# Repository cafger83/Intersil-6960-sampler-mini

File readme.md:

This board set is a small and light version of the original Intersil 6960 Sampler board.
Schematic based on the manual of the original board.
The CPU (IM6101) is a one-chip implementation of the legendary DEC PDP-8 computer's CPU

Boards:
IM6100 SAMPLER mini - main board with CPU, serial port, 1kword ROM monitor and 256 kword RAM

IM6100 HID - human interface device with status leds, address display, 12x input switches

IM6100 RAM+IO - 2kword RAM extension, 2x12bit GPIO

Original board:
https://computermuseum.informatik.uni-stuttgart.de/dev_en/im6100sp/

Original manual:
http://dunfield.classiccmp.org/other/i6100cfs.pdf

*** UNDER DEVELOPMENT! Not tested, not validated yet. ***

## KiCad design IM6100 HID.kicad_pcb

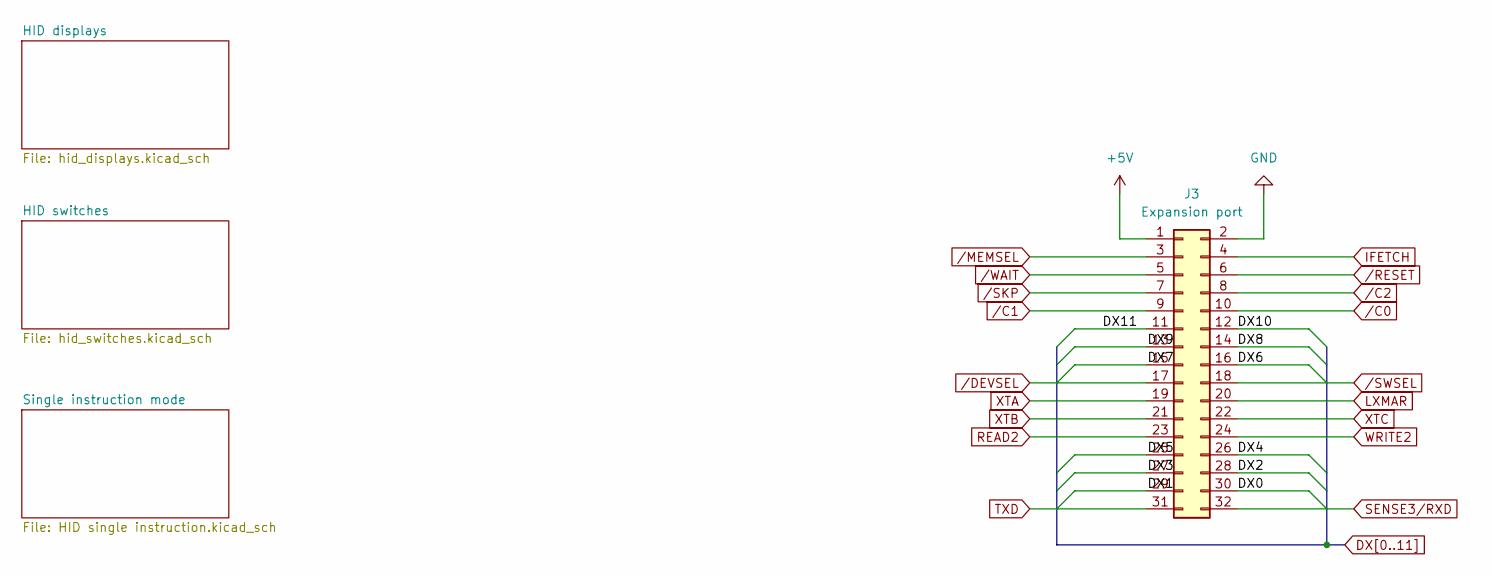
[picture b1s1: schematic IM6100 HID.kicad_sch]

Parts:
J3: Expansion port; PinHeader_2x16_P2.54mm_Vertical

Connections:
+5V: J3.1; also elsewhere on the board
DX0: J3.30; also elsewhere on the board
DX1: J3.29; also elsewhere on the board
DX2: J3.28; also elsewhere on the board
DX3: J3.27; also elsewhere on the board
DX4: J3.26; also elsewhere on the board
DX5: J3.25; also elsewhere on the board
DX6: J3.16; also elsewhere on the board
DX7: J3.15; also elsewhere on the board
DX8: J3.14; also elsewhere on the board
DX9: J3.13; also elsewhere on the board
DX10: J3.12; also elsewhere on the board
DX11: J3.11; also elsewhere on the board
GND: J3.2; also elsewhere on the board
IFETCH: J3.4; also elsewhere on the board
LXMAR: J3.20; also elsewhere on the board
READ2: J3.23
TXD: J3.31; also elsewhere on the board
WRITE2: J3.24
XTA: J3.19
XTB: J3.21; also elsewhere on the board
XTC: J3.22; also elsewhere on the board
/C0: J3.10
/C1: J3.9
/C2: J3.8
/RESET: J3.6; also elsewhere on the board
/SKP: J3.7
/WAIT: J3.5; also elsewhere on the board

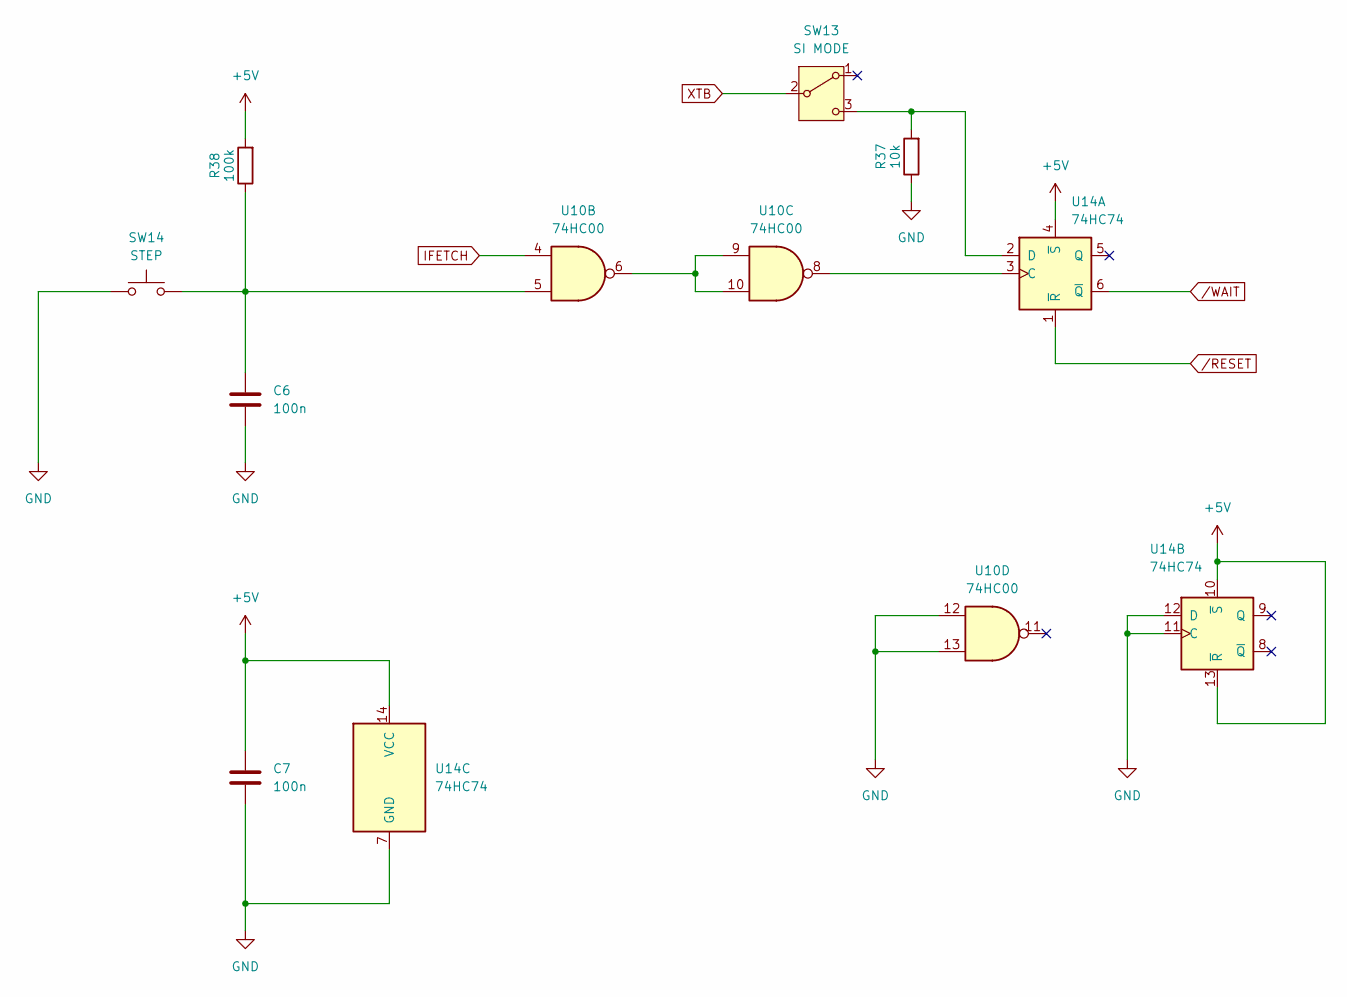
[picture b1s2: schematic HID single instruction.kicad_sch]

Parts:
C6, C7: 100n; C_0805_2012Metric_Pad1.18x1.45mm_HandSolder
R37: 10k; R_0805_2012Metric
R38: 100k; R_0805_2012Metric
SW13: SI MODE; PinHeader_1x03_P2.54mm_Vertical
SW14: STEP; SW_PUSH_6mm_H4.3mm
U10: 74HC00; SO-14_3.9x8.65mm_P1.27mm
U14: 74HC74; SO-14_3.9x8.65mm_P1.27mm

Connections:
+5V: C7.1, R38.2, U14.4 (~S), U14.10 (~S), U14.13 (~R), U14.14 (VCC); also elsewhere on the board
GND: C6.2, C7.2, R37.1, SW14.1, U10.12, U10.13, U14.7 (GND), U14.11 (C), U14.12 (D); also elsewhere on the board
IFETCH: U10.4; also elsewhere on the board
unnamed: C6.1, R38.1, SW14.2, U10.5
unnamed: R37.2, SW13.3 (C), U14.2 (D)
unnamed: U10.6, U10.9, U10.10
unnamed: U10.8, U14.3 (C)
XTB: SW13.2 (B); also elsewhere on the board
/RESET: U14.1 (~R); also elsewhere on the board
/WAIT: U14.6 (~Q); also elsewhere on the board

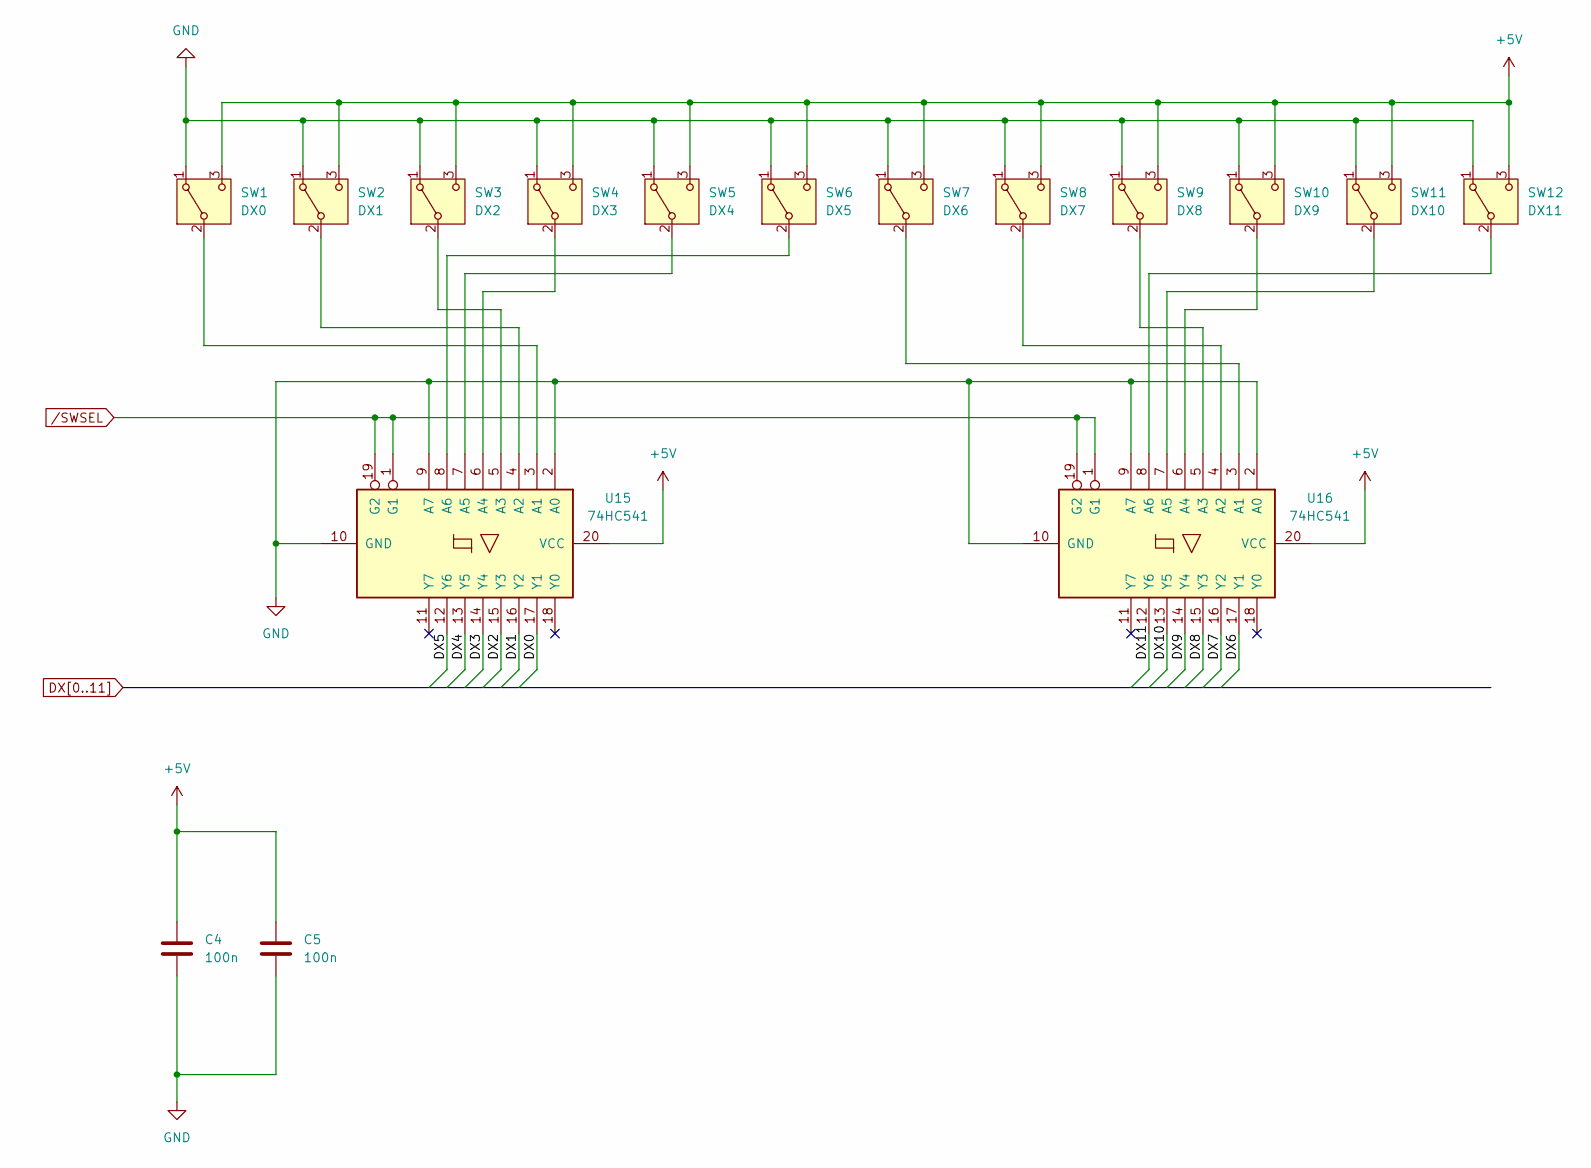
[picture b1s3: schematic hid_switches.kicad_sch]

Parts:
C4, C5: 100n; C_0805_2012Metric_Pad1.18x1.45mm_HandSolder
SW1: DX0; PinHeader_1x03_P2.54mm_Vertical
SW2: DX1; PinHeader_1x03_P2.54mm_Vertical
SW3: DX2; PinHeader_1x03_P2.54mm_Vertical
SW4: DX3; PinHeader_1x03_P2.54mm_Vertical
SW5: DX4; PinHeader_1x03_P2.54mm_Vertical
SW6: DX5; PinHeader_1x03_P2.54mm_Vertical
SW7: DX6; PinHeader_1x03_P2.54mm_Vertical
SW8: DX7; PinHeader_1x03_P2.54mm_Vertical
SW9: DX8; PinHeader_1x03_P2.54mm_Vertical
SW10: DX9; PinHeader_1x03_P2.54mm_Vertical
SW11: DX10; PinHeader_1x03_P2.54mm_Vertical
SW12: DX11; PinHeader_1x03_P2.54mm_Vertical
U15, U16: 74HC541; SO-20_12.8x7.5mm_P1.27mm

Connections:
+5V: C4.1, C5.1, SW1.3 (C), SW2.3 (C), SW3.3 (C), SW4.3 (C), SW5.3 (C), SW6.3 (C), SW7.3 (C), SW8.3 (C), SW9.3 (C), SW10.3 (C), SW11.3 (C), SW12.3 (C), U15.20 (VCC), U16.20 (VCC); also elsewhere on the board
DX0: U15.17 (Y1); also elsewhere on the board
DX1: U15.16 (Y2); also elsewhere on the board
DX2: U15.15 (Y3); also elsewhere on the board
DX3: U15.14 (Y4); also elsewhere on the board
DX4: U15.13 (Y5); also elsewhere on the board
DX5: U15.12 (Y6); also elsewhere on the board
DX6: U16.17 (Y1); also elsewhere on the board
DX7: U16.16 (Y2); also elsewhere on the board
DX8: U16.15 (Y3); also elsewhere on the board
DX9: U16.14 (Y4); also elsewhere on the board
DX10: U16.13 (Y5); also elsewhere on the board
DX11: U16.12 (Y6); also elsewhere on the board
GND: C4.2, C5.2, SW1.1 (A), SW2.1 (A), SW3.1 (A), SW4.1 (A), SW5.1 (A), SW6.1 (A), SW7.1 (A), SW8.1 (A), SW9.1 (A), SW10.1 (A), SW11.1 (A), SW12.1 (A), U15.2 (A0), U15.9 (A7), U15.10 (GND), U16.2 (A0), U16.9 (A7), U16.10 (GND); also elsewhere on the board
unnamed: SW1.2 (B), U15.3 (A1)
unnamed: SW2.2 (B), U15.4 (A2)
unnamed: SW3.2 (B), U15.5 (A3)
unnamed: SW4.2 (B), U15.6 (A4)
unnamed: SW5.2 (B), U15.7 (A5)
unnamed: SW6.2 (B), U15.8 (A6)
unnamed: SW7.2 (B), U16.3 (A1)
unnamed: SW8.2 (B), U16.4 (A2)
unnamed: SW9.2 (B), U16.5 (A3)
unnamed: SW10.2 (B), U16.6 (A4)
unnamed: SW11.2 (B), U16.7 (A5)
unnamed: SW12.2 (B), U16.8 (A6)

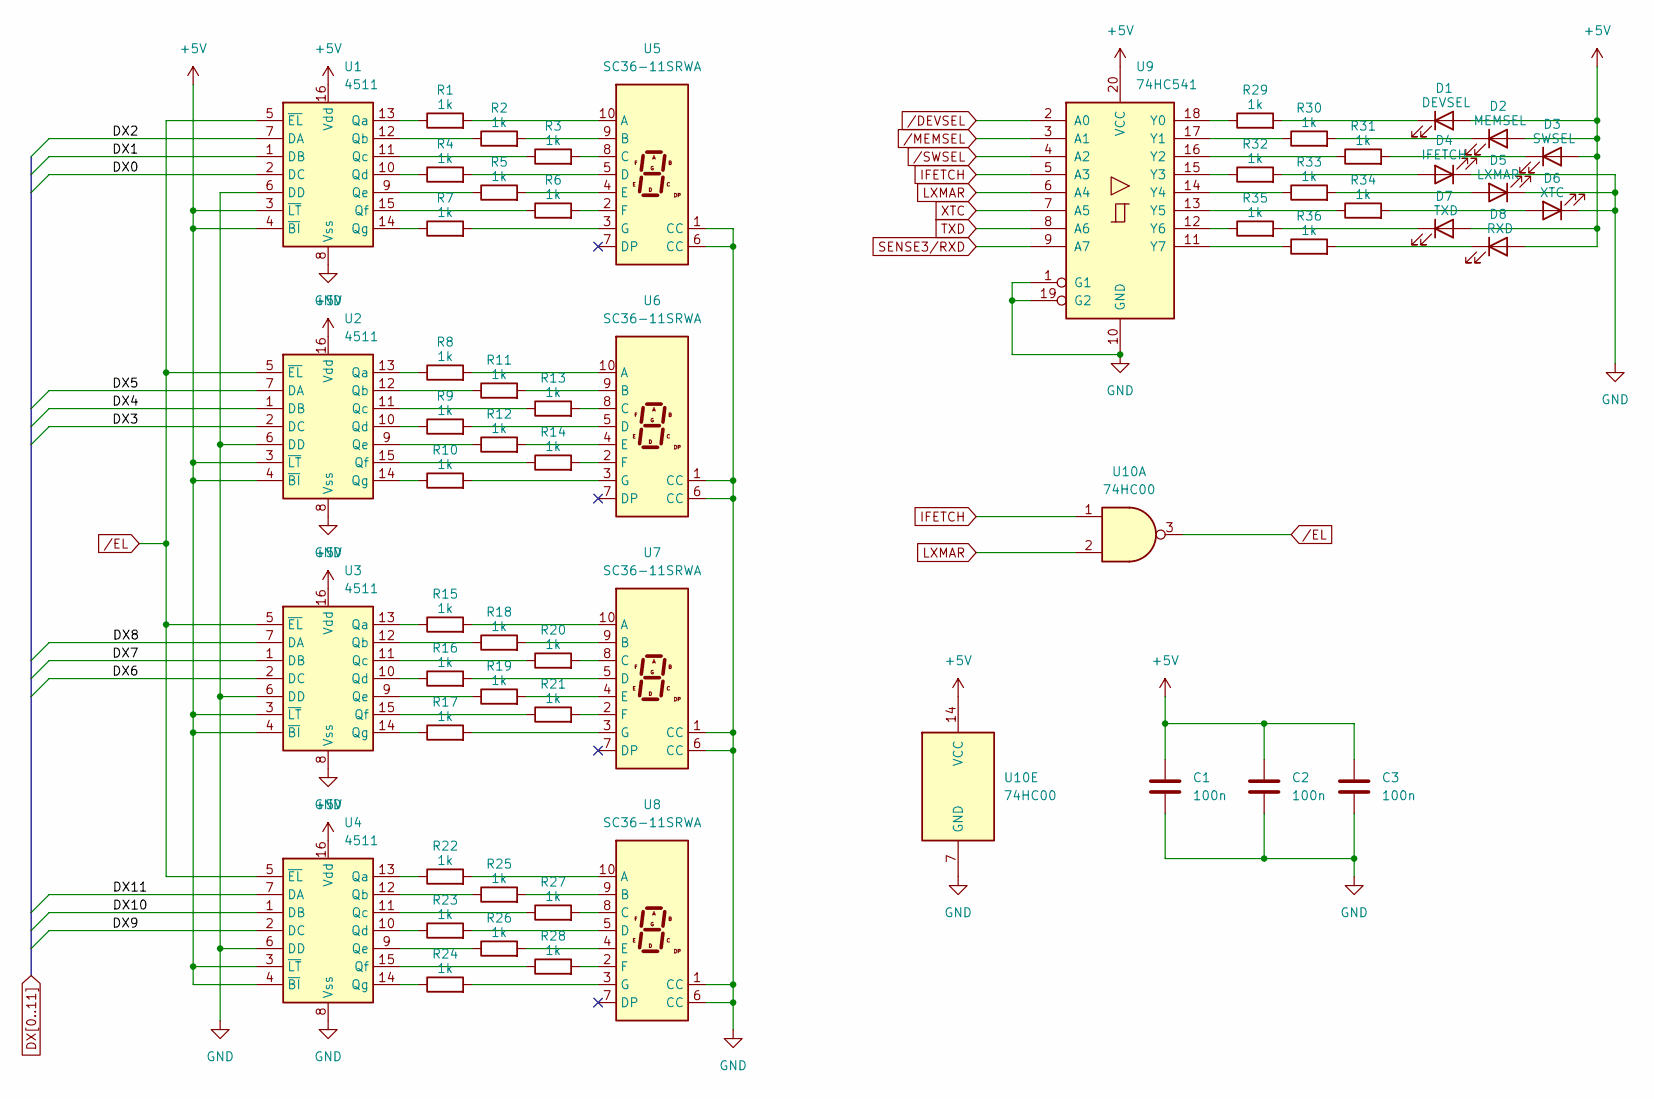
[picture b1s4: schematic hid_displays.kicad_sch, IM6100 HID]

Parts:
C1, C2, C3: 100n; C_0805_2012Metric_Pad1.18x1.45mm_HandSolder
D1: DEVSEL; LED_1206_3216Metric
D2: MEMSEL; LED_1206_3216Metric
D3: SWSEL; LED_1206_3216Metric
D4: IFETCH; LED_1206_3216Metric
D5: LXMAR; LED_1206_3216Metric
D6: XTC; LED_1206_3216Metric
D7: TXD; LED_1206_3216Metric
D8: RXD; LED_1206_3216Metric
R1, R2, R3, R4, R5, R6, R7, R8, R9, R10, R11, R12, R13, R14, R15, R16, R17, R18, R19, R20, R21, R22, R23, R24, R25, R26, R27, R28, R29, R30, R31, R32, R33, R34, R35, R36: 1k; R_0805_2012Metric
U1, U2, U3, U4: 4511; SO-16_3.9x9.9mm_P1.27mm
U5, U6, U7, U8: SC36-11SRWA; HDSP-A151
U9: 74HC541; SO-20_12.8x7.5mm_P1.27mm
U10: 74HC00; SO-14_3.9x8.65mm_P1.27mm

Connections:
+5V: C1.1, C2.1, C3.1, D1.2 (A), D2.2 (A), D3.2 (A), D7.2 (A), D8.2 (A), U1.3 (~LT), U1.4 (~BI), U1.16 (Vdd), U2.3 (~LT), U2.4 (~BI), U2.16 (Vdd), U3.3 (~LT), U3.4 (~BI), U3.16 (Vdd), U4.3 (~LT), U4.4 (~BI), U4.16 (Vdd), U9.20 (VCC), U10.14 (VCC); also elsewhere on the board
DX0: U1.2 (DC); also elsewhere on the board
DX1: U1.1 (DB); also elsewhere on the board
DX2: U1.7 (DA); also elsewhere on the board
DX3: U2.2 (DC); also elsewhere on the board
DX4: U2.1 (DB); also elsewhere on the board
DX5: U2.7 (DA); also elsewhere on the board
DX6: U3.2 (DC); also elsewhere on the board
DX7: U3.1 (DB); also elsewhere on the board
DX8: U3.7 (DA); also elsewhere on the board
DX9: U4.2 (DC); also elsewhere on the board
DX10: U4.1 (DB); also elsewhere on the board
DX11: U4.7 (DA); also elsewhere on the board
GND: C1.2, C2.2, C3.2, D4.1 (K), D5.1 (K), D6.1 (K), U1.6 (DD), U1.8 (Vss), U2.6 (DD), U2.8 (Vss), U3.6 (DD), U3.8 (Vss), U4.6 (DD), U4.8 (Vss), U5.1 (CC), U5.6 (CC), U6.1 (CC), U6.6 (CC), U7.1 (CC), U7.6 (CC), U8.1 (CC), U8.6 (CC), U9.1 (G1), U9.10 (GND), U9.19 (G2), U10.7 (GND); also elsewhere on the board
IFETCH: U9.5 (A3), U10.1; also elsewhere on the board
LXMAR: U9.6 (A4), U10.2; also elsewhere on the board
unnamed: D1.1 (K), R29.2
unnamed: D2.1 (K), R30.2
unnamed: D3.1 (K), R31.2
unnamed: D4.2 (A), R32.2
unnamed: D5.2 (A), R33.2
unnamed: D6.2 (A), R34.2
unnamed: D7.1 (K), R35.2
unnamed: D8.1 (K), R36.2
unnamed: R1.1, U1.13 (Qa)
unnamed: R2.1, U1.12 (Qb)
unnamed: R3.1, U1.11 (Qc)
unnamed: R4.1, U1.10 (Qd)
unnamed: R5.1, U1.9 (Qe)
unnamed: R6.1, U1.15 (Qf)
unnamed: R7.1, U1.14 (Qg)
unnamed: R8.1, U2.13 (Qa)
unnamed: R11.1, U2.12 (Qb)
unnamed: R13.1, U2.11 (Qc)
unnamed: R9.1, U2.10 (Qd)
unnamed: R12.1, U2.9 (Qe)
unnamed: R14.1, U2.15 (Qf)
unnamed: R10.1, U2.14 (Qg)
unnamed: R15.1, U3.13 (Qa)
unnamed: R18.1, U3.12 (Qb)
unnamed: R20.1, U3.11 (Qc)
unnamed: R16.1, U3.10 (Qd)
unnamed: R19.1, U3.9 (Qe)
unnamed: R21.1, U3.15 (Qf)
unnamed: R17.1, U3.14 (Qg)
unnamed: R22.1, U4.13 (Qa)
unnamed: R25.1, U4.12 (Qb)
unnamed: R27.1, U4.11 (Qc)
unnamed: R23.1, U4.10 (Qd)
unnamed: R26.1, U4.9 (Qe)
unnamed: R28.1, U4.15 (Qf)
unnamed: R24.1, U4.14 (Qg)
unnamed: R1.2, U5.10 (A)
unnamed: R2.2, U5.9 (B)
unnamed: R3.2, U5.8 (C)
unnamed: R4.2, U5.5 (D)
unnamed: R5.2, U5.4 (E)
unnamed: R6.2, U5.2 (F)
unnamed: R7.2, U5.3 (G)
unnamed: R8.2, U6.10 (A)
unnamed: R11.2, U6.9 (B)
unnamed: R13.2, U6.8 (C)
unnamed: R9.2, U6.5 (D)
unnamed: R12.2, U6.4 (E)
unnamed: R14.2, U6.2 (F)
unnamed: R10.2, U6.3 (G)
unnamed: R15.2, U7.10 (A)
unnamed: R18.2, U7.9 (B)
unnamed: R20.2, U7.8 (C)
unnamed: R16.2, U7.5 (D)
unnamed: R19.2, U7.4 (E)
unnamed: R21.2, U7.2 (F)
unnamed: R17.2, U7.3 (G)
unnamed: R22.2, U8.10 (A)
unnamed: R25.2, U8.9 (B)
unnamed: R27.2, U8.8 (C)
unnamed: R23.2, U8.5 (D)
unnamed: R26.2, U8.4 (E)
unnamed: R28.2, U8.2 (F)
unnamed: R24.2, U8.3 (G)
unnamed: R29.1, U9.18 (Y0)
unnamed: R30.1, U9.17 (Y1)
unnamed: R31.1, U9.16 (Y2)
unnamed: R32.1, U9.15 (Y3)
unnamed: R33.1, U9.14 (Y4)
unnamed: R34.1, U9.13 (Y5)
unnamed: R35.1, U9.12 (Y6)
unnamed: R36.1, U9.11 (Y7)
TXD: U9.8 (A6); also elsewhere on the board
XTC: U9.7 (A5); also elsewhere on the board
/EL: U1.5 (~EL), U2.5 (~EL), U3.5 (~EL), U4.5 (~EL), U10.3

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
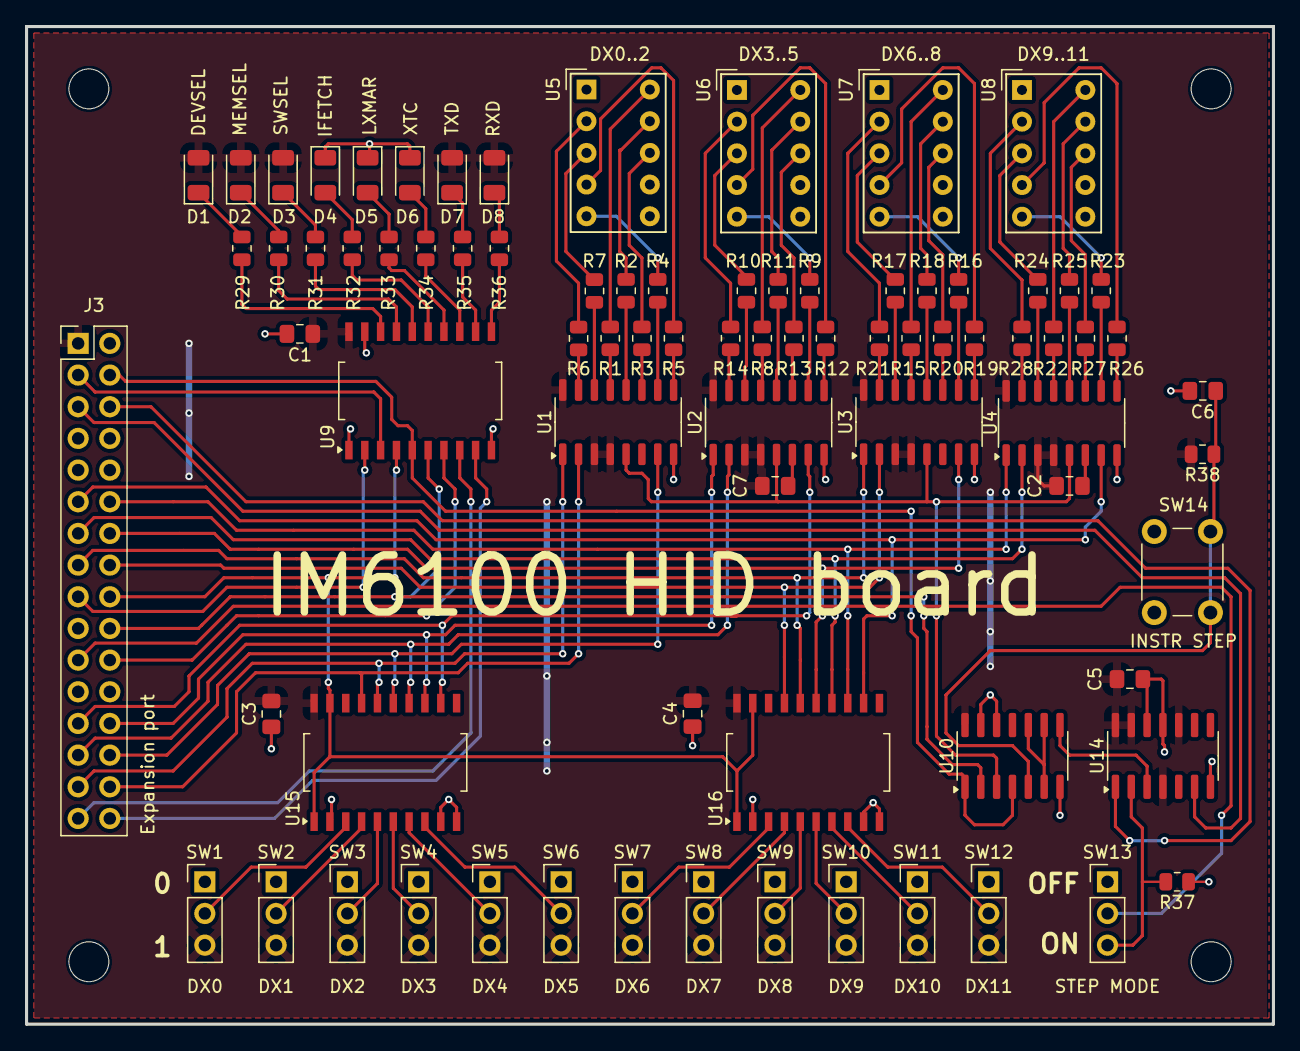
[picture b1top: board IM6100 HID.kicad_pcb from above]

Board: 2 copper layers, 100.0 x 80.0 mm, 85 parts (0 on the bottom side), 114 nets.

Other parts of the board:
HOLE1, HOLE2, HOLE3, HOLE4: MountingHole_3.2mm_M3

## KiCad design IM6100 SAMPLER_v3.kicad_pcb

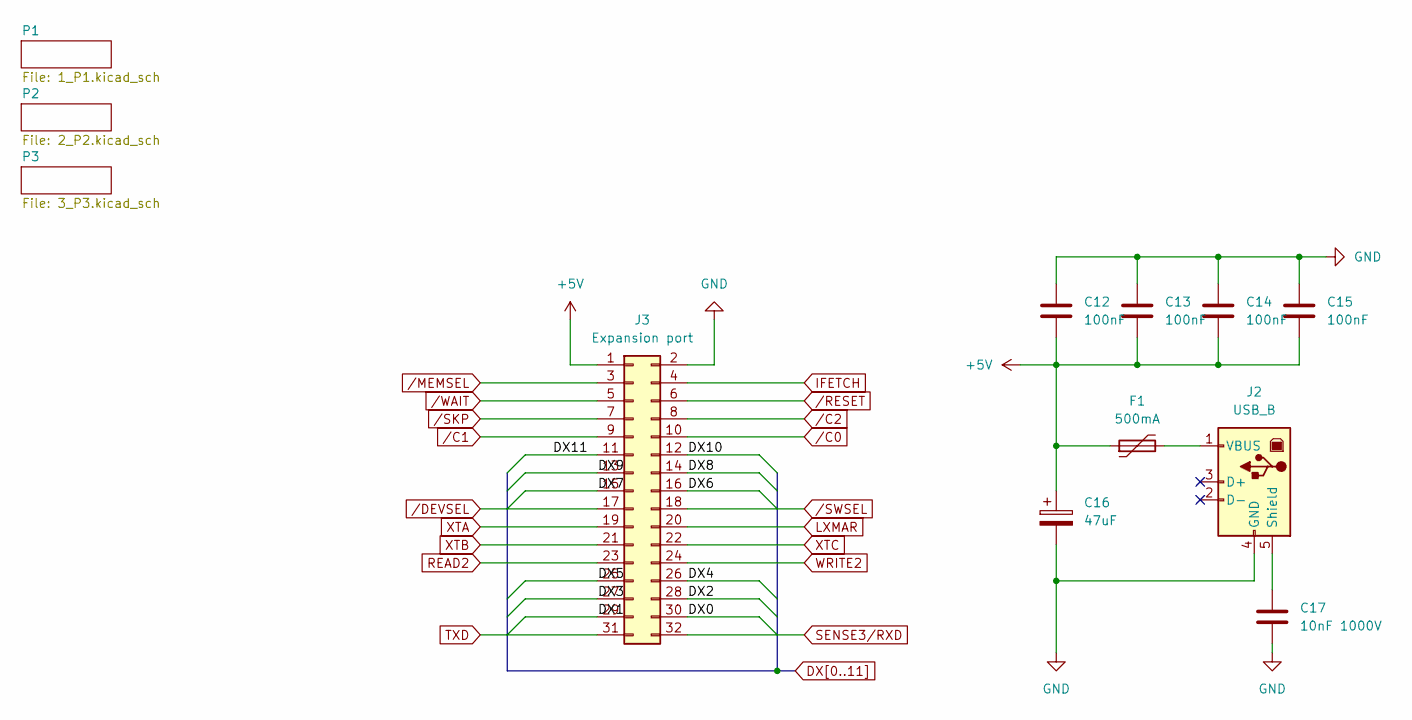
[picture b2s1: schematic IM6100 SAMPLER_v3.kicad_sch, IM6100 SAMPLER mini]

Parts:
C12, C13, C14, C15: 100nF; C_Disc_D5.0mm_W2.5mm_P2.50mm
C16: 47uF; CP_Radial_D6.3mm_P2.50mm
C17: 10nF 1000V; C_Disc_D5.0mm_W2.5mm_P2.50mm
F1: 500mA; C_Disc_D6.0mm_W2.5mm_P5.00mm
J2: USB_B; USB_B_Lumberg_2411_02_Horizontal
J3: Expansion port; PinHeader_2x16_P2.54mm_Vertical

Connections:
+5V: C12.2, C13.2, C14.2, C15.2, C16.1, F1.1, J3.1; also elsewhere on the board
DX0: J3.30; also elsewhere on the board
DX1: J3.29; also elsewhere on the board
DX2: J3.28; also elsewhere on the board
DX3: J3.27; also elsewhere on the board
DX4: J3.26; also elsewhere on the board
DX5: J3.25; also elsewhere on the board
DX6: J3.16; also elsewhere on the board
DX7: J3.15; also elsewhere on the board
DX8: J3.14; also elsewhere on the board
DX9: J3.13; also elsewhere on the board
DX10: J3.12; also elsewhere on the board
DX11: J3.11; also elsewhere on the board
GND: C12.1, C13.1, C14.1, C15.1, C16.2, C17.2, J2.4 (GND), J3.2; also elsewhere on the board
IFETCH: J3.4; also elsewhere on the board
LXMAR: J3.20; also elsewhere on the board
unnamed: C17.1, J2.5 (Shield)
unnamed: F1.2, J2.1 (VBUS)
READ2: J3.23; also elsewhere on the board
SENSE3/RXD: J3.32; also elsewhere on the board
TXD: J3.31; also elsewhere on the board
WRITE2: J3.24; also elsewhere on the board
XTA: J3.19; also elsewhere on the board
XTB: J3.21; also elsewhere on the board
XTC: J3.22; also elsewhere on the board
/C0: J3.10; also elsewhere on the board
/C1: J3.9; also elsewhere on the board
/C2: J3.8; also elsewhere on the board
/DEVSEL: J3.17; also elsewhere on the board
/MEMSEL: J3.3; also elsewhere on the board
/SKP: J3.7; also elsewhere on the board
/SWSEL: J3.18; also elsewhere on the board
/WAIT: J3.5; also elsewhere on the board

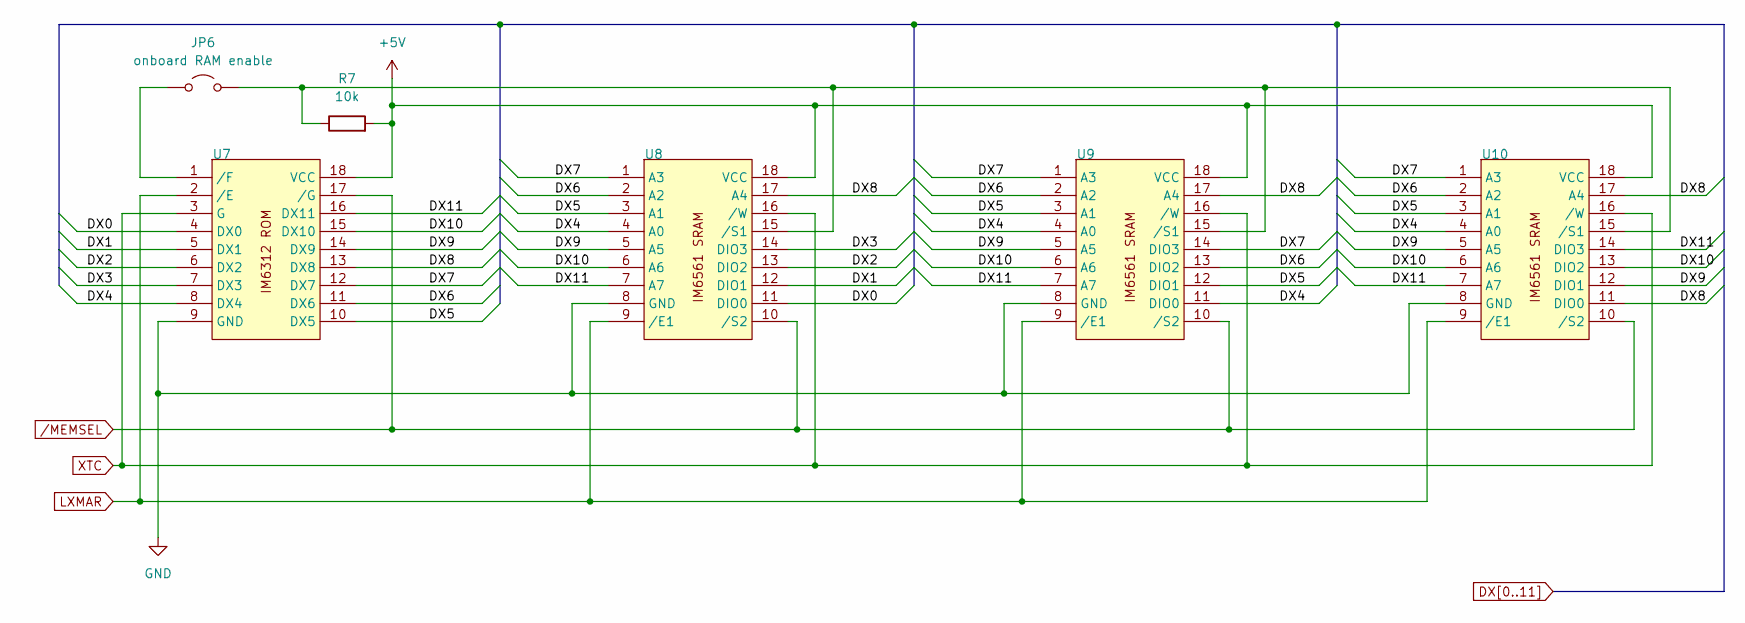
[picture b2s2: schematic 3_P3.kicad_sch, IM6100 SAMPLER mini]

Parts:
JP6: onboard RAM enable; PinHeader_1x02_P2.54mm_Vertical
R7: 10k; R_Axial_DIN0207_L6.3mm_D2.5mm_P7.62mm_Horizontal
U7, U8, U9, U10: DIP-18_W7.62mm_Socket

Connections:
+5V: R7.2, U7.18 (VCC), U8.18 (VCC), U9.18 (VCC), U10.18 (VCC); also elsewhere on the board
DX0: U7.4 (DX0), U8.11 (DIO0); also elsewhere on the board
DX1: U7.5 (DX1), U8.12 (DIO1); also elsewhere on the board
DX2: U7.6 (DX2), U8.13 (DIO2); also elsewhere on the board
DX3: U7.7 (DX3), U8.14 (DIO3); also elsewhere on the board
DX4: U7.8 (DX4), U8.4 (A0), U9.4 (A0), U9.11 (DIO0), U10.4 (A0); also elsewhere on the board
DX5: U7.10 (DX5), U8.3 (A1), U9.3 (A1), U9.12 (DIO1), U10.3 (A1); also elsewhere on the board
DX6: U7.11 (DX6), U8.2 (A2), U9.2 (A2), U9.13 (DIO2), U10.2 (A2); also elsewhere on the board
DX7: U7.12 (DX7), U8.1 (A3), U9.1 (A3), U9.14 (DIO3), U10.1 (A3); also elsewhere on the board
DX8: U7.13 (DX8), U8.17 (A4), U9.17 (A4), U10.11 (DIO0), U10.17 (A4); also elsewhere on the board
DX9: U7.14 (DX9), U8.5 (A5), U9.5 (A5), U10.5 (A5), U10.12 (DIO1); also elsewhere on the board
DX10: U7.15 (DX10), U8.6 (A6), U9.6 (A6), U10.6 (A6), U10.13 (DIO2); also elsewhere on the board
DX11: U7.16 (DX11), U8.7 (A7), U9.7 (A7), U10.7 (A7), U10.14 (DIO3); also elsewhere on the board
GND: U7.9 (GND), U8.8 (GND), U9.8 (GND), U10.8 (GND); also elsewhere on the board
LXMAR: U7.2 (/E), U8.9 (/E1), U9.9 (/E1), U10.9 (/E1); also elsewhere on the board
unnamed: JP6.1 (A), U7.1 (/F)
unnamed: JP6.2 (B), R7.1, U8.15 (/S1), U9.15 (/S1), U10.15 (/S1)
XTC: U7.3 (G), U8.16 (/W), U9.16 (/W), U10.16 (/W); also elsewhere on the board
/MEMSEL: U7.17 (/G), U8.10 (/S2), U9.10 (/S2), U10.10 (/S2); also elsewhere on the board

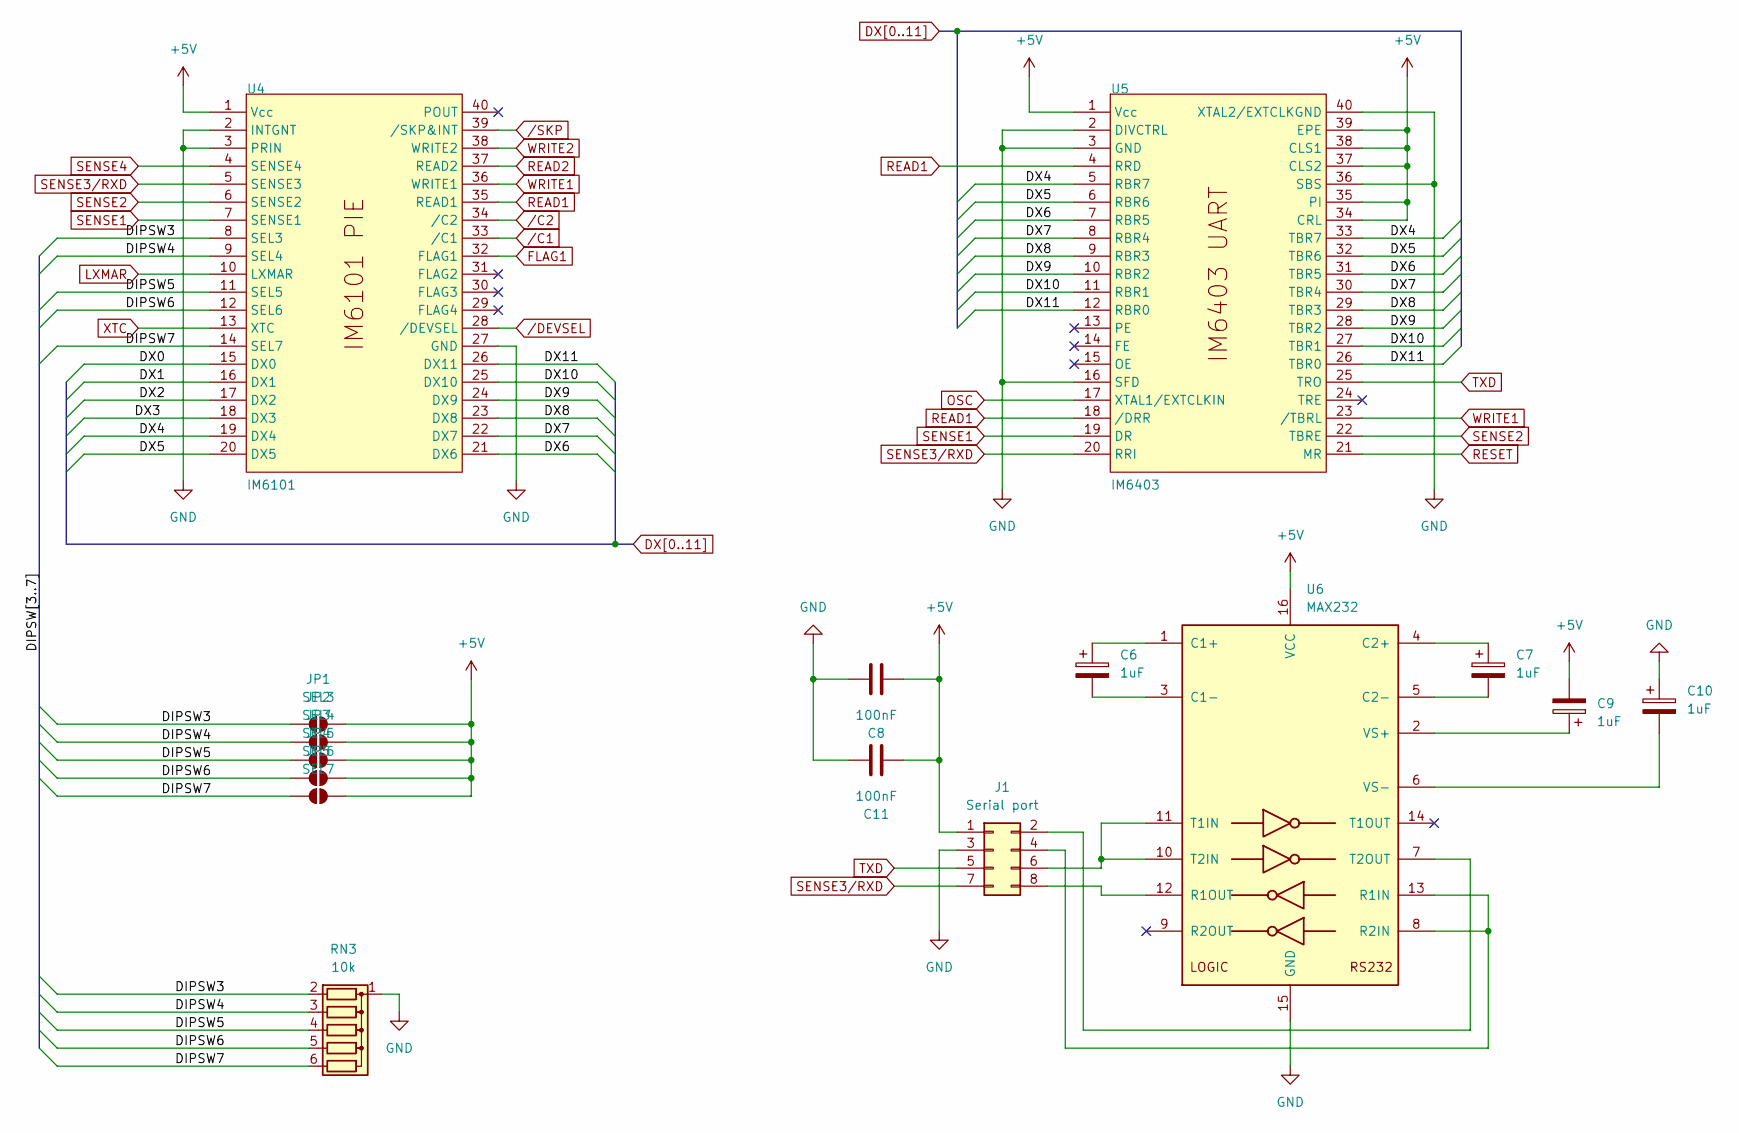
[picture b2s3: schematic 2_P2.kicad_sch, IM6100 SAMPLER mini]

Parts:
C6, C7, C9, C10: 1uF; C_Disc_D5.0mm_W2.5mm_P2.50mm
C8, C11: 100nF; C_Disc_D5.0mm_W2.5mm_P2.50mm
J1: Serial port; PinHeader_2x04_P2.54mm_Vertical
JP1: SEL3; SolderJumper-2_P1.3mm_Open_Pad1.0x1.5mm
JP2: SEL4; SolderJumper-2_P1.3mm_Open_Pad1.0x1.5mm
JP3: SEL5; SolderJumper-2_P1.3mm_Open_Pad1.0x1.5mm
JP4: SEL6; SolderJumper-2_P1.3mm_Open_Pad1.0x1.5mm
JP5: SEL7; SolderJumper-2_P1.3mm_Open_Pad1.0x1.5mm
RN3: 10k; R_Array_SIP6
U4: IM6101; DIP-40_W15.24mm_Socket
U5: IM6403; DIP-40_W15.24mm_Socket
U6: MAX232; DIP-16_W7.62mm_Socket

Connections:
+5V: C8.1, C9.2, C11.1, J1.1, JP1.2 (B), JP2.2 (B), JP3.2 (B), JP4.2 (B), JP5.2 (B), U4.1 (Vcc), U5.1 (Vcc), U5.34 (CRL), U5.35 (PI), U5.37 (CLS2), U5.38 (CLS1), U5.39 (EPE), U6.16 (VCC); also elsewhere on the board
/P2/DIPSW3: JP1.1 (A), RN3.2 (R1), U4.8 (SEL3)
/P2/DIPSW4: JP2.1 (A), RN3.3 (R2), U4.9 (SEL4)
/P2/DIPSW5: JP3.1 (A), RN3.4 (R3), U4.11 (SEL5)
/P2/DIPSW6: JP4.1 (A), RN3.5 (R4), U4.12 (SEL6)
/P2/DIPSW7: JP5.1 (A), RN3.6 (R5), U4.14 (SEL7)
DX0: U4.15 (DX0); also elsewhere on the board
DX1: U4.16 (DX1); also elsewhere on the board
DX2: U4.17 (DX2); also elsewhere on the board
DX3: U4.18 (DX3); also elsewhere on the board
DX4: U4.19 (DX4), U5.5 (RBR7), U5.33 (TBR7); also elsewhere on the board
DX5: U4.20 (DX5), U5.6 (RBR6), U5.32 (TBR6); also elsewhere on the board
DX6: U4.21 (DX6), U5.7 (RBR5), U5.31 (TBR5); also elsewhere on the board
DX7: U4.22 (DX7), U5.8 (RBR4), U5.30 (TBR4); also elsewhere on the board
DX8: U4.23 (DX8), U5.9 (RBR3), U5.29 (TBR3); also elsewhere on the board
DX9: U4.24 (DX9), U5.10 (RBR2), U5.28 (TBR2); also elsewhere on the board
DX10: U4.25 (DX10), U5.11 (RBR1), U5.27 (TBR1); also elsewhere on the board
DX11: U4.26 (DX11), U5.12 (RBR0), U5.26 (TBR0); also elsewhere on the board
FLAG1: U4.32 (FLAG1); also elsewhere on the board
GND: C8.2, C10.1, C11.2, J1.3, RN3.1 (common), U4.2 (INTGNT), U4.3 (PRIN), U4.27 (GND), U5.2 (DIVCTRL), U5.3 (GND), U5.16 (SFD), U5.36 (SBS), U5.40 (XTAL2/EXTCLKGND), U6.15 (GND); also elsewhere on the board
LXMAR: U4.10 (LXMAR); also elsewhere on the board
unnamed: J1.2, U6.7 (T2OUT)
unnamed: J1.4, U6.8 (R2IN), U6.13 (R1IN)
unnamed: J1.6, U6.10 (T2IN), U6.11 (T1IN)
unnamed: J1.8, U6.12 (R1OUT)
unnamed: C6.1, U6.1 (C1+)
unnamed: C6.2, U6.3 (C1-)
unnamed: C7.1, U6.4 (C2+)
unnamed: C7.2, U6.5 (C2-)
unnamed: C9.1, U6.2 (VS+)
unnamed: C10.2, U6.6 (VS-)
OSC: U5.17 (XTAL1/EXTCLKIN); also elsewhere on the board
READ1: U4.35 (READ1), U5.4 (RRD), U5.18 (/DRR)
READ2: U4.37 (READ2); also elsewhere on the board
RESET: U5.21 (MR); also elsewhere on the board
SENSE1: U4.7 (SENSE1), U5.19 (DR)
SENSE2: U4.6 (SENSE2), U5.22 (TBRE)
SENSE3/RXD: J1.7, U4.5 (SENSE3), U5.20 (RRI); also elsewhere on the board
SENSE4: U4.4 (SENSE4); also elsewhere on the board
TXD: J1.5, U5.25 (TRO); also elsewhere on the board
WRITE1: U4.36 (WRITE1), U5.23 (/TBRL)
WRITE2: U4.38 (WRITE2); also elsewhere on the board
XTC: U4.13 (XTC); also elsewhere on the board
/C1: U4.33 (/C1); also elsewhere on the board
/C2: U4.34 (/C2); also elsewhere on the board
/DEVSEL: U4.28 (/DEVSEL); also elsewhere on the board
/SKP: U4.39 (/SKP&INT); also elsewhere on the board
